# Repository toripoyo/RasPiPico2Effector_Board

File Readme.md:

Raspberry Pi Pico2 でつくる簡単エフェクターです。  
KiCadプロジェクトは本リポジトリ、Raspberry Pi Pico2 のソフトウェアは [RasPiPico2Effector_Software](https://github.com/toripoyo/RasPiPico2Effector_Software) を参照してください。

## スペック

| パラメータ | 値 |
|-----------|-------|
| MCU | RP2350 (Cortex-M33) @ 250 MHz |
| サンプリングレート | 約44.1 kHz|
| オーバーサンプリング | 4倍 |
| 信号処理ブロックサイズ | 16サンプル |
| ADC分解能 | 12ビット |
| PWM分解能 | 11ビット |
| PWM周波数 | 約122 kHz (250 MHz / PWM分解能) |
| Core 0 | ADC入力/DMA、PWM出力、UI/ディスプレイ |
| Core 1 | オーディオエフェクト処理 |

※ in/out のアナログLPFはfc=15kHzです。

## 操作方法
- On/Thru: エフェクトOn/Off
- Enter: エフェクト種類の切り替え
- Up/Down: 操作パラメータ選択
- Left/Right: パラメータ変更

## 書き込み方法
Reset ボタンを押しながら、RasPi Pico上のBOOTSELボタンを押し、PCからストレージとして認識される状態にしてください。

## ライセンス
[LICENSE](./LICENSE)

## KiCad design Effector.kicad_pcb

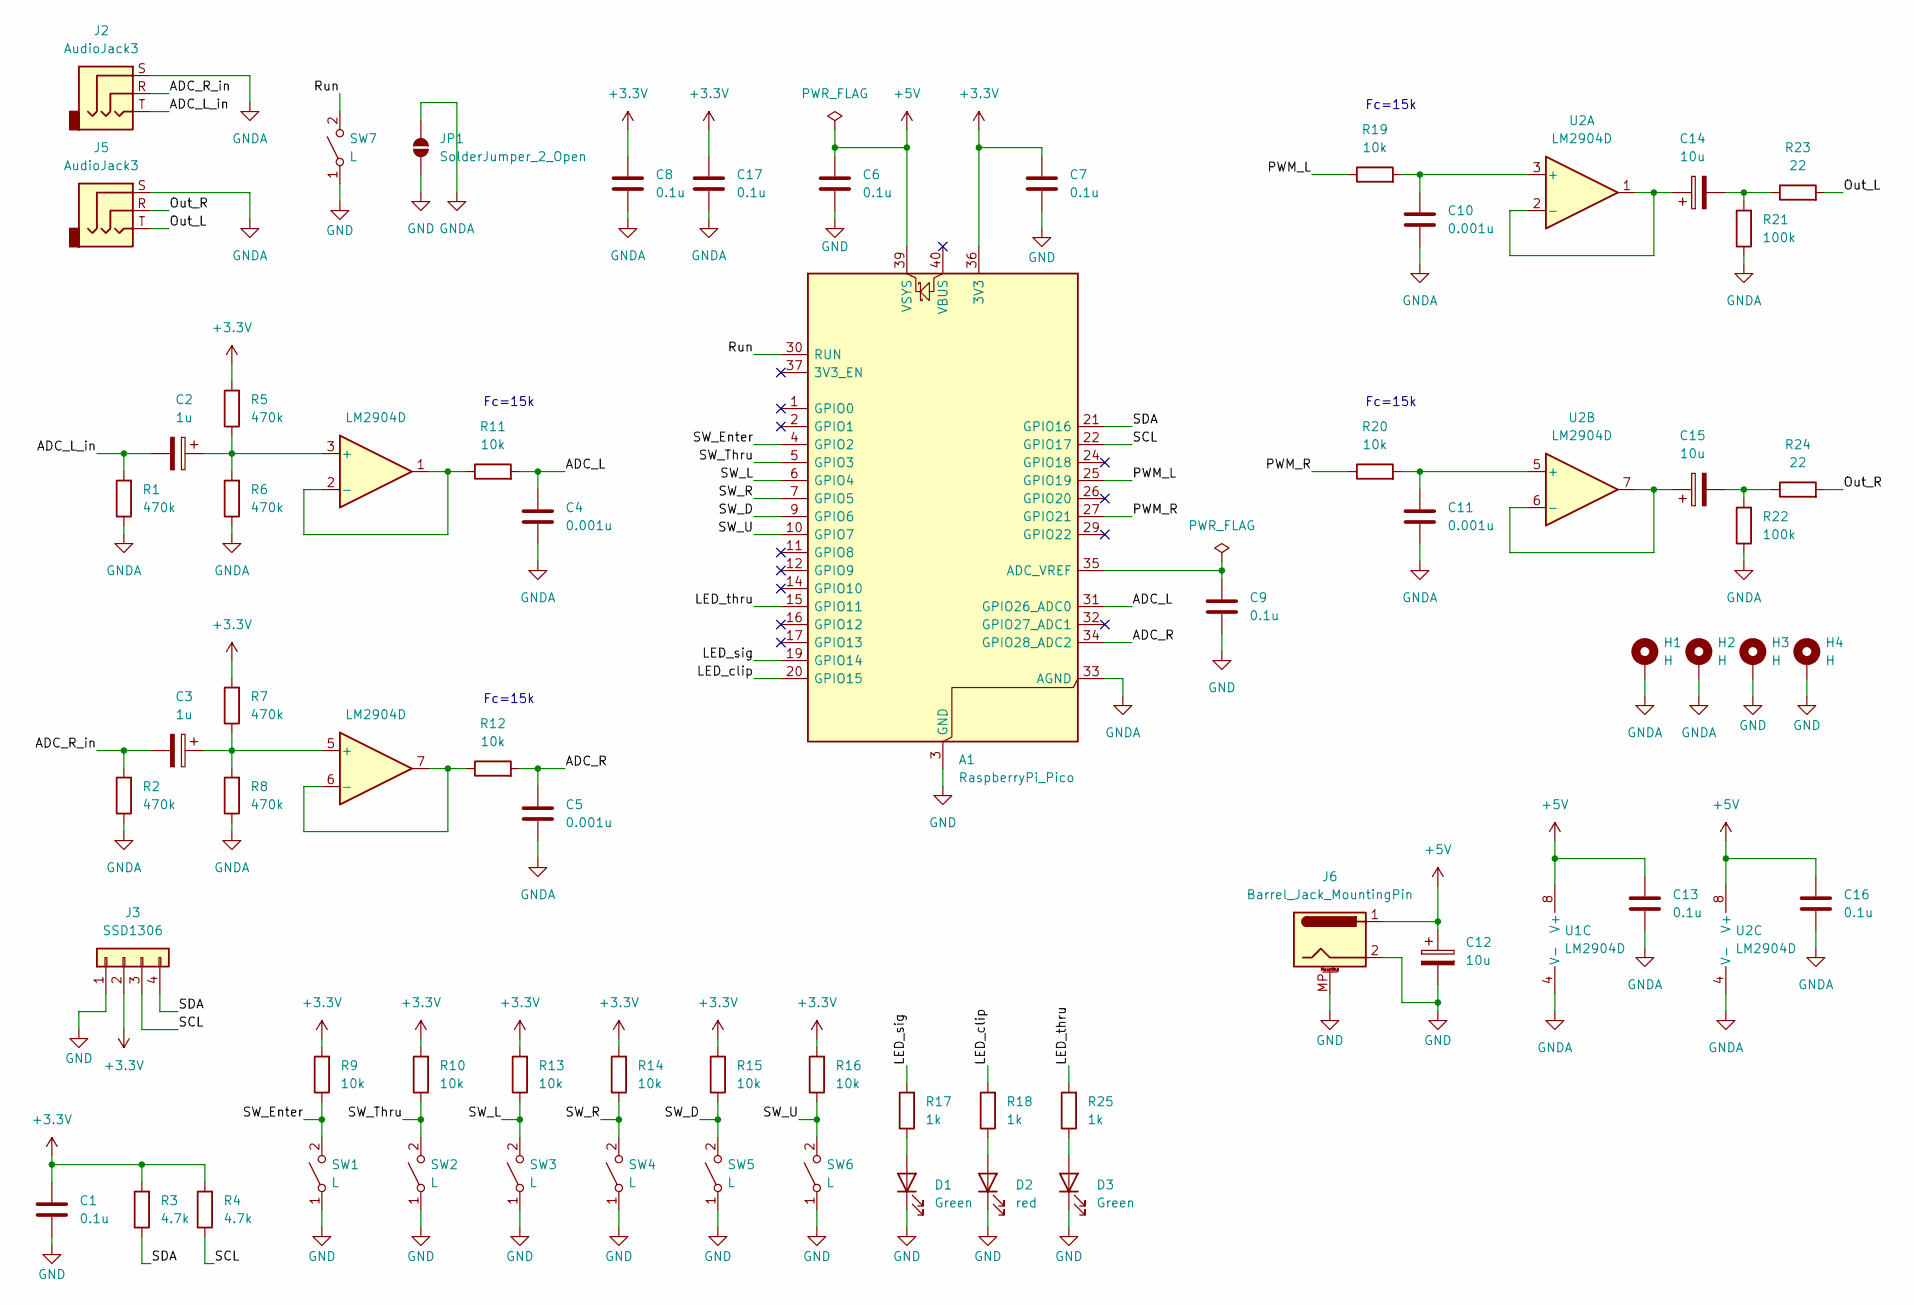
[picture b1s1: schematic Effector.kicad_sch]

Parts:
A1: RaspberryPi_Pico; RaspberryPi_Pico_Common_Unspecified
C1, C6, C7, C8, C9, C13, C16, C17: 0.1u; C_0603_1608Metric
C2, C3: 1u; CP_Radial_D5.0mm_P2.00mm
C4, C5, C10, C11: 0.001u; C_0603_1608Metric
C12, C14, C15: 10u; CP_Radial_D5.0mm_P2.00mm
D1, D3: Green; LED_0603_1608Metric
D2: red; LED_0603_1608Metric
H1, H2, H3, H4: H; MountingHole_3.2mm_M3_Pad
J2, J5: AudioJack3; Jack_3.5mm_Switronic_ST-005-G_horizontal
J3: SSD1306
J6: Barrel_Jack_MountingPin; BarrelJack_Horizontal
JP1: SolderJumper_2_Open; SolderJumper-2_P1.3mm_Open_RoundedPad1.0x1.5mm
R1, R2, R5, R6, R7, R8: 470k; R_0603_1608Metric
R3, R4: 4.7k; R_0603_1608Metric
R9, R10, R11, R12, R13, R14, R15, R16, R19, R20: 10k; R_0603_1608Metric
R17, R18, R25: 1k; R_0603_1608Metric
R21, R22: 100k; R_0603_1608Metric
R23, R24: 22; R_0603_1608Metric
SW1, SW2, SW3, SW4, SW5, SW6, SW7: L; SW_PUSH_6mm_H4.3mm
U1, U2: LM2904D; SOIC-8_3.9x4.9mm_P1.27mm

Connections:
+3.3V: A1.36 (3V3), C1.1, C7.1, C8.1, C17.1, J3.2, R3.2, R4.2, R5.2, R7.2, R9.2, R10.2, R13.2, R14.2, R15.2, R16.2
+5V: A1.39 (VSYS), C6.1, C12.1, C13.1, C16.1, J6.1, U1.8 (V+), U2.8 (V+)
/ADC_L: A1.31 (GPIO26_ADC0), C4.1, R11.2
/ADC_L_in: C2.2, J2.T, R1.2
/ADC_R: A1.34 (GPIO28_ADC2), C5.1, R12.2
/ADC_R_in: C3.2, J2.R, R2.2
/LED_clip: A1.20 (GPIO15), R18.2
/LED_sig: A1.19 (GPIO14), R17.2
/LED_thru: A1.15 (GPIO11), R25.2
/Out_L: J5.T, R23.2
/Out_R: J5.R, R24.2
/PWM_L: A1.25 (GPIO19), R19.1
/PWM_R: A1.27 (GPIO21), R20.1
/Run: A1.30 (RUN), SW7.2 (B)
/SCL: A1.22 (GPIO17), J3.3, R4.1
/SDA: A1.21 (GPIO16), J3.4, R3.1
/SW_D: A1.9 (GPIO6), R15.1, SW5.2 (B)
/SW_Enter: A1.4 (GPIO2), R9.1, SW1.2 (B)
/SW_L: A1.6 (GPIO4), R13.1, SW3.2 (B)
/SW_R: A1.7 (GPIO5), R14.1, SW4.2 (B)
/SW_Thru: A1.5 (GPIO3), R10.1, SW2.2 (B)
/SW_U: A1.10 (GPIO7), R16.1, SW6.2 (B)
GND: A1.3 (GND), A1.8 (GND), A1.13 (GND), A1.18 (GND), A1.23 (GND), A1.28 (GND), A1.38 (GND), C1.2, C6.2, C7.2, C9.2, C12.2, D1.1 (K), D2.1 (K), D3.1 (K), H3.1, H4.1, J3.1, J6.2, J6.MP (MountPin), JP1.1 (A), SW1.1 (A), SW2.1 (A), SW3.1 (A), SW4.1 (A), SW5.1 (A), SW6.1 (A), SW7.1 (A)
GNDA: A1.33 (AGND), C4.2, C5.2, C8.2, C10.2, C11.2, C13.2, C16.2, C17.2, H1.1, H2.1, J2.S, J5.S, JP1.2 (B), R1.1, R2.1, R6.1, R8.1, R21.1, R22.1, U1.4 (V-), U2.4 (V-)
unnamed: A1.35 (ADC_VREF), C9.1
unnamed: C14.2, R21.2, R23.1
unnamed: C15.2, R22.2, R24.1
unnamed: D1.2 (A), R17.1
unnamed: D2.2 (A), R18.1
unnamed: D3.2 (A), R25.1
unnamed: C2.1, R5.1, R6.2, U1.3 (+)
unnamed: R11.1, U1.1, U1.2 (-)
unnamed: C3.1, R7.1, R8.2, U1.5 (+)
unnamed: R12.1, U1.6 (-), U1.7
unnamed: C10.1, R19.2, U2.3 (+)
unnamed: C14.1, U2.1, U2.2 (-)
unnamed: C11.1, R20.2, U2.5 (+)
unnamed: C15.1, U2.6 (-), U2.7

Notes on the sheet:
Fc=15k

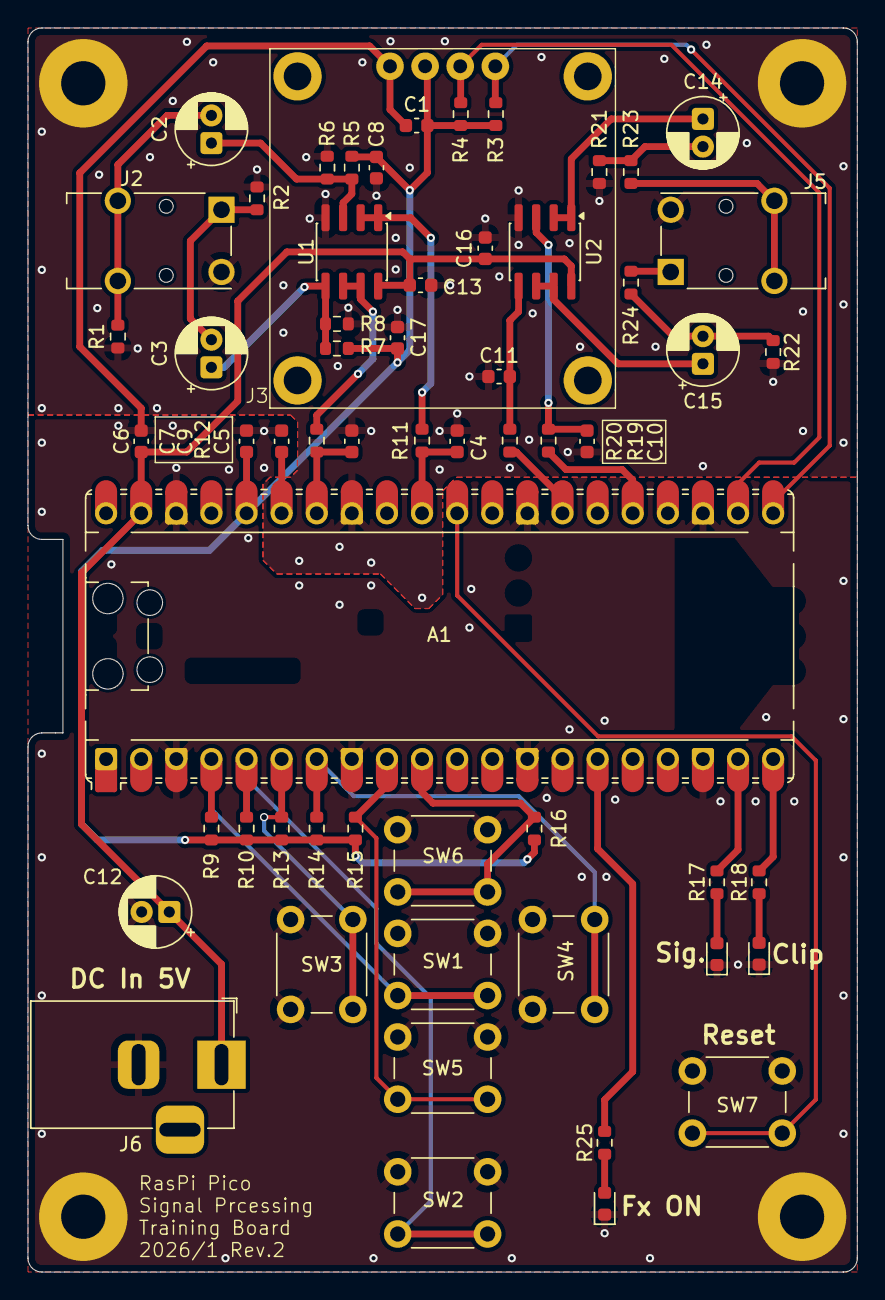
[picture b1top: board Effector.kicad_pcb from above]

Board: 2 copper layers, 60.0 x 90.0 mm, 64 parts (1 on the bottom side), 38 nets.

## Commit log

2026-01-11 Add Circuit
2026-01-11 ドキュメントを追加
